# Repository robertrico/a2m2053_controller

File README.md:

# A2M2053 Controller

A replacement controller board for the Apple UniDisk 3.5 (A2M2053).

## Overview

The UniDisk 3.5 is Apple's 800K drive for the Apple II. When its controller
board (IF-83, service part 661-0307) dies, there's nothing to fix it with. The
board is built around a Sony CXD1013 gate array that has no public datasheet
and no replacement, and the only spare board on eBay has sat unsold at $150
for months.

This project replaces the whole board. A Raspberry Pi RP2350 speaks SmartPort
to the Apple IIe through the Liron card and drives the stock Sony 800K
mechanism directly through its 20-pin connector. The 65C02, ROM, RAM, IWM and
the CXD1013 are all gone. The mechanism, the case and the front panel stay.

It isn't a clone of the original. The firmware is new C on the Pico SDK. The
original drive ROM is used as a test oracle for SmartPort behavior, status
codes, errors and timing, never as a template.

## Features

- SmartPort device on the Liron card: STATUS, READBLOCK, WRITEBLOCK, FORMAT,
  CONTROL (eject), INIT
- Reads, writes and formats 800K double-sided ProDOS disks
- Daisy chain out the rear DB-19, in front of or behind another drive
- Front-panel eject button and in-use LED
- Runs from the Apple's own +5V and +12V rails through the host cable
- Whole-track read buffer on its own core; every write verified on the next
  revolution
- USB console for bring-up: mechanism status, raw flux capture, block reads,
  whole-disk scans, bus counters

## Scope

Apple IIe with 800K double-sided ProDOS disks. Macintosh disks (524-byte
blocks, Mac interleave) and 400K single-sided disks show up in Apple's docs
and the drive ROM but were never used on the IIe, so they're out of scope.

## Specifications

| Parameter | Value |
|---|---|
| MCU | RP2350A on a Raspberry Pi Pico 2 (prototype) |
| Level shifting | 5x SN74LVC8T245, 3.3V to 5V, one DIR and /OE per 8 channels |
| GPIO | 25 of 26 used |
| Host interface | SmartPort, Liron card DB-19 (CN102) |
| Mechanism interface | Sony 800K 20-pin (CN104, ERS 699-0321) |
| Mechanism | Stock Sony 800K double-sided, CX23077A logic + CX20185 read/write amp |
| Rear port | DB-19 daisy chain: PH3_OUT, ENBL_OUT, LASTONE/ |
| Power | +5V and +12V from the host connector; Pico VSYS from +5V through a diode |

## Architecture

```
 Apple IIe / Liron card                                  Sony 800K mechanism
         | DB-19                                                | 20-pin
   [level shifters]                                    [level shifters]
         |                                                      |
   PIO0: SmartPort FM rx/tx                     PIO1: flux capture / GCR write
   PIO2: rear-port pass-through                                 |
         |                                                      |
   CORE 0: SmartPort device  <---- block request queue ---->  CORE 1: mechanism
   - bus phases, packets                                      - status, seek, motor, eject
   - commands, DIB, status                                    - speed zones
   - daisy-chain ID, LASTONE/                                 - whole-track buffer
                                                              - GCR decode/encode
```

Each SmartPort read, write or format becomes a request to core 1. Core 0
holds ACK until the answer is back, and the Liron card waits.

## Project status

**Perfboard prototype: done** (October 2026). Milestones M0 to M9 passed on
the bench with a Pico 2, five 8T245 breakout boards and a mechanism from a
dead UniDisk.

| Milestone | What | Log |
|---|---|---|
| M0 | Bench rig, power, shifter boot safety | [m0](docs/build_log/m0.md) |
| M1 | Mechanism status reads | [m1](docs/build_log/m1.md) |
| M2 | Mechanism commands: motor, seek, eject | [m2](docs/build_log/m2.md) |
| M3 | Raw flux capture, decoded on the Mac | [m3](docs/build_log/m3.md) |
| M4 | Whole disk read on the board | [m4](docs/build_log/m4.md) |
| M5 | Write and format; the working UniDisk reads our disk | [m5](docs/build_log/m5.md) |
| M6 | SmartPort on the RP2350; ProDOS boots from a RAM disk | [m6](docs/build_log/m6.md) |
| M7 | ProDOS boots from a real floppy through the Liron card | [m7](docs/build_log/m7.md) |
| M7.5 | Bench supply retired; runs on the IIe rails | [m7_5](docs/build_log/m7_5.md) |
| M8 | Daisy chain with a working UniDisk, both orders | [m8](docs/build_log/m8.md) |
| M9 | Disk swaps, write-protect, ejects, resets, long runs | [m9](docs/build_log/m9.md) |

**Drop-in PCB: in design.** The outline matches the IF-83 and fits the
original mounting holes and case opening (checked with 3D prints). The board
must stay hand-solderable and well under the $150 the spare board couldn't
sell for. Requirements carried from the bench: [FABRICATION.md](FABRICATION.md).

Build notes and photos are also on
[bytehamr.com](https://bytehamr.com/projects/unidisk-controller/).

## Repository structure

```
a2m2053_controller/
├── firmware/            # RP2350 firmware (C, Pico SDK)
│   ├── src/             # SmartPort, mechanism server, PIO programs, console
│   └── test/            # Host-side unit tests (fake drive, simulated Liron card)
├── tools/
│   ├── a2m/             # Python: console client, flux decode, GCR, PIO model
│   ├── apple/           # Test disk builders and SPCOMPARE (Applesoft)
│   └── tests/           # pytest
├── hardware/kicad/      # KiCad schematic and PCB
├── docs/
│   ├── build_log/       # Per-milestone notes and measurements
│   ├── captures/        # Scope shots, Apple screens, console logs
│   ├── photos/          # Bench photos
│   ├── superpowers/specs/  # Design spec
│   ├── research_notes.md   # Facts with sources; start here
│   ├── level_shifting.md   # Signal directions and shifter grouping
│   └── pin_budget.md       # GPIO map
└── FABRICATION.md       # PCB requirements and part choices
```

## Getting started

### Prerequisites

- [Pico SDK](https://github.com/raspberrypi/pico-sdk) 2.2.0, CMake, Ninja,
  arm-none-eabi-gcc
- A Raspberry Pi Debug Probe (or picoprobe) and Raspberry Pi's OpenOCD build
  for SWD flashing
- Python 3 for the tools (`tools/requirements.txt`)
- [AppleCommander](https://applecommander.github.io/) and
  [ADTPro](https://adtpro.com/) for the test disks

### Building and flashing

```bash
cd firmware
make            # build
make test       # host-side unit tests
make flash      # program over SWD (OpenOCD)
make reset      # reset the target
```

Tool paths live in `.env.local` at the repo root, git-ignored. Copy
`.env.example`, fill in `PICO_SDK_PATH` and, if they are not on your PATH,
`OPENOCD` and `GDB`. Anything already in your environment or on the `make`
command line wins over the file. The test-disk scripts in `tools/apple/` read
`AC_JAR` and `PRODOS_SRC` from the same file.

### Console

The firmware exposes a USB CDC console. `help` lists the commands: mechanism
status and control, flux capture, block reads and writes, whole-disk scans,
format, and `sp` for the SmartPort bus state and counters. The Python tool
drives the console for the scripted jobs:

```bash
cd tools
python -m a2m.cli readdisk --port /dev/cu.usbmodemXXXX --out disk.po --compare ref.po
```

## Design references

This project builds on:

- [Byte Hamr](https://github.com/robertrico/project_byte_hamr): the PicoPort
  SmartPort device for the RP2040 (the FM receive/transmit PIO programs and
  packet layout started there), its IWM work, and the annotated drive ROM
  disassembly by Eric Smith used as the oracle.
- [bitsavers](http://www.bitsavers.org/pdf/apple/disk/sony/): Sony 800K
  drive ERS (699-0321), mechanism schematics, Apple drive command and status
  codes.
- [tashnotes](https://github.com/lampmerchant/tashnotes): GCR checksum and
  drive command tables.
- Apple II Technical Notes (UniDisk 3.5 #1-#5, Misc #6) and the IWM
  specifications, via the [Asimov archive](https://www.apple.asimov.net/).

Datasheets, Apple and Sony documents, and photos of other people's boards
were used during the work but aren't ours to host, so they're not in this
repo. [docs/SOURCES.md](docs/SOURCES.md) says where each one came from.

## License

This project is released under the [MIT License](LICENSE.md).

## Author

Robert Rico

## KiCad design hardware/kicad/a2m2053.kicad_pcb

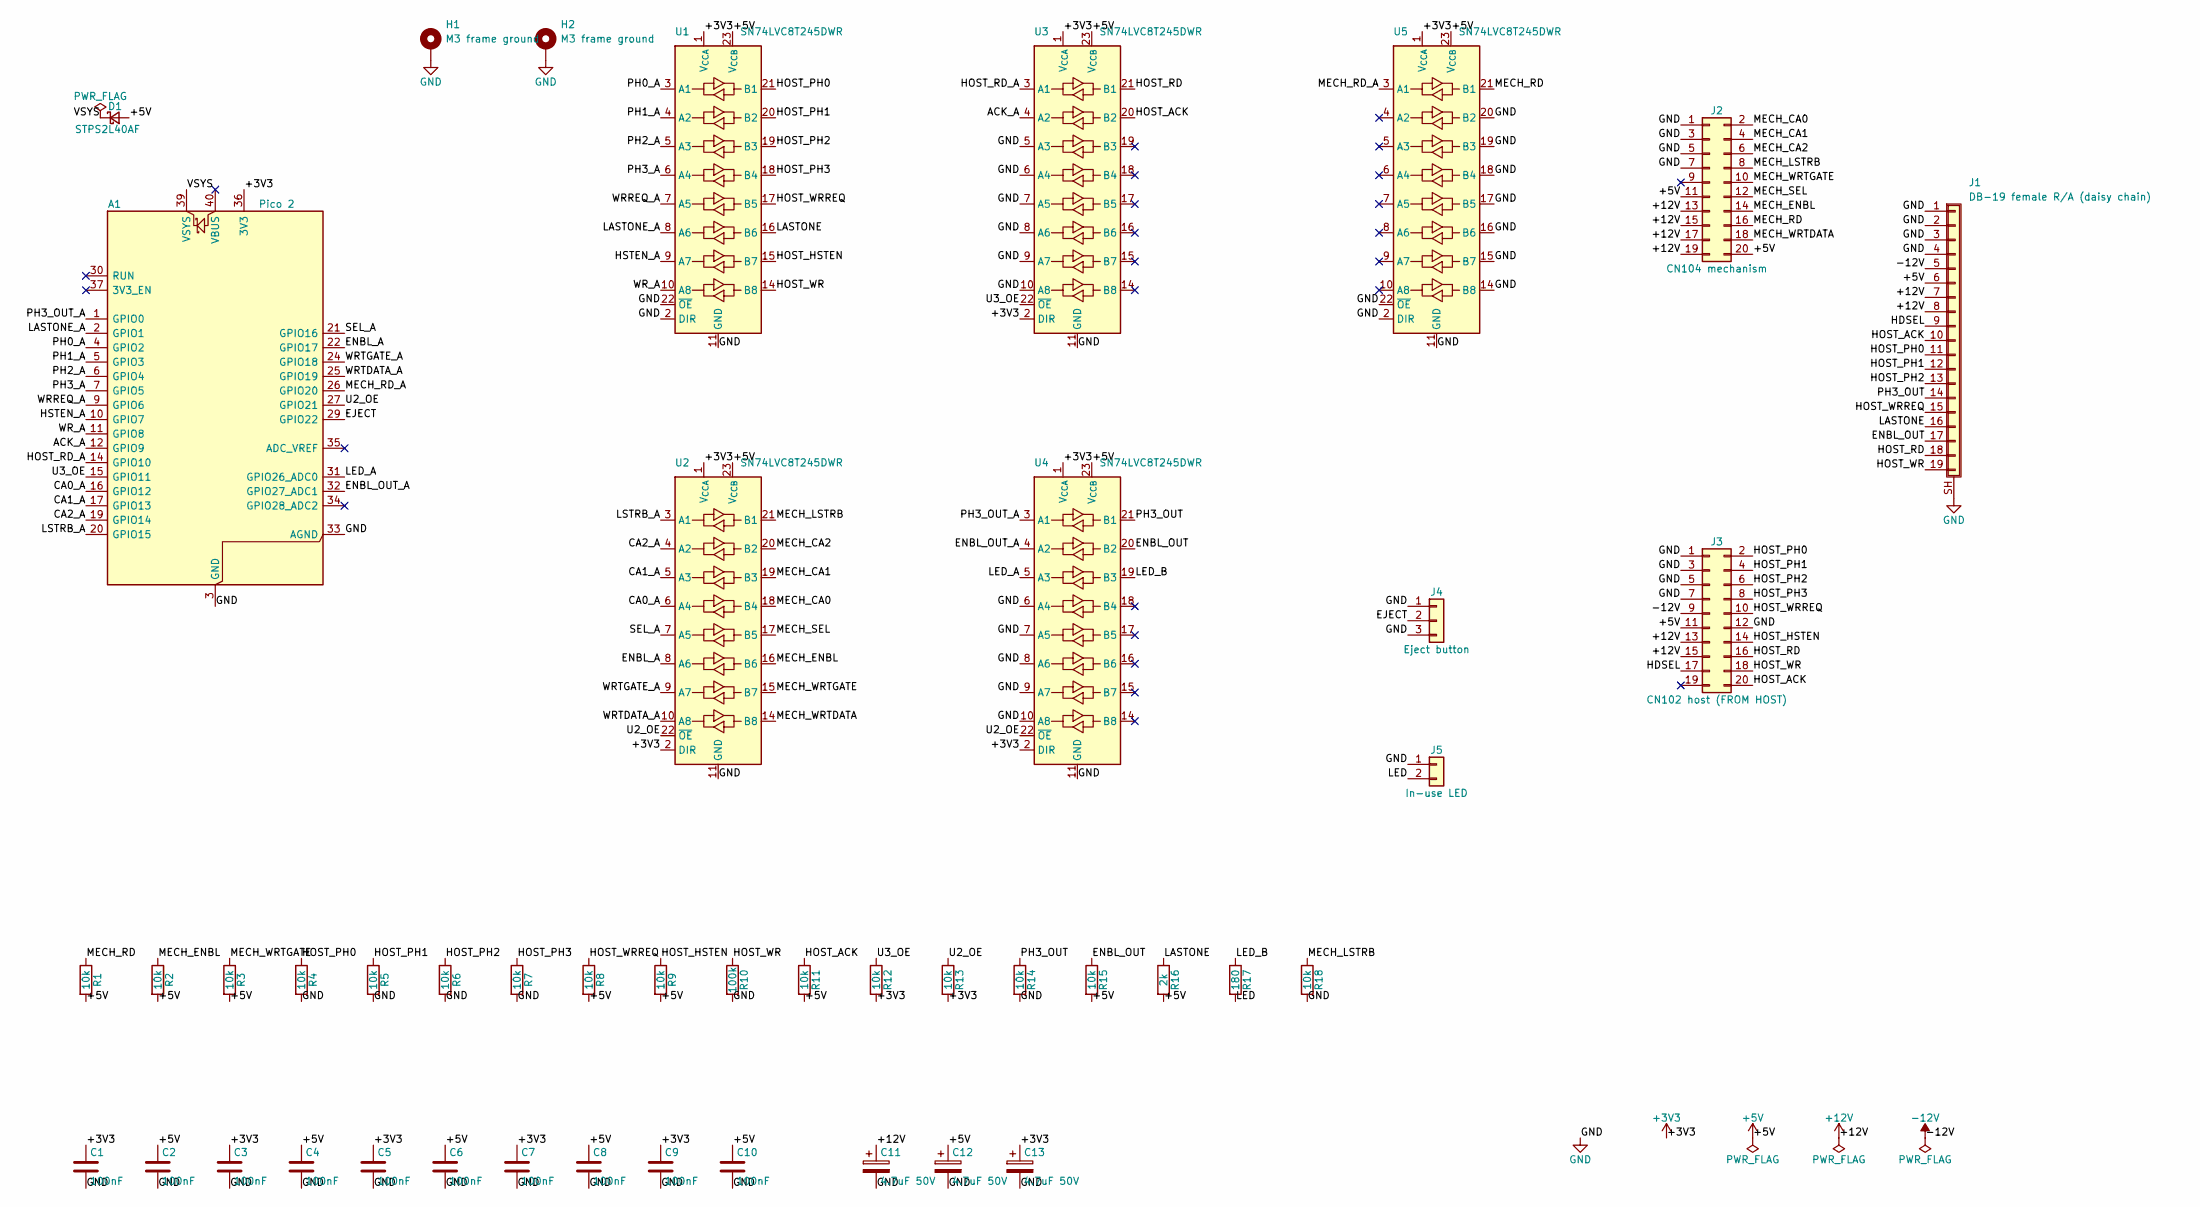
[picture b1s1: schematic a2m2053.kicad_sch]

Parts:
A1: Pico 2; RaspberryPi_Pico_SMD_HandSolder
C1, C2, C3, C4, C5, C6, C7, C8, C9, C10: 100nF; C_0805_2012Metric
C11, C12, C13: 4.7uF 50V; CP_Radial_D5.0mm_P2.00mm
D1: STPS2L40AF; D_SMA
H1: M3 frame ground; MountingHole_3.2mm_M3_Pad_5.2mm
H2: M3 frame ground; MountingHole_3.2mm_M3_Pad_Via
J1: DB-19 female R/A (daisy chain); DSUB-19_Female_Horizontal_P2.77x2.84mm_MountingHoles38.8mm
J2: CN104 mechanism; IDC-Header_2x10_P2.54mm_Vertical
J3: CN102 host (FROM HOST); IDC-Header_2x10_P2.54mm_Vertical
J4: Eject button; TE_AMP_CT_1x03_P2.00mm_Vertical; MPN 292161-3
J5: In-use LED; TE_AMP_CT_1x02_P2.00mm_Vertical; MPN 292161-2
R1, R2, R3, R4, R5, R6, R7, R8, R9, R11, R12, R13, R14, R15, R18: 10k; R_1206_3216Metric
R10: 100k; R_1206_3216Metric
R16: 2k; R_1206_3216Metric
R17: 180; R_1206_3216Metric
U1, U2, U3, U4, U5: SN74LVC8T245DWR; SOIC-24W_7.5x15.4mm_P1.27mm

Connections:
+3V3: A1.36 (3V3), C1.1, C3.1, C5.1, C7.1, C9.1, C13.1, R12.2, R13.2, U1.1 (V_{CCA}), U2.1 (V_{CCA}), U2.2 (DIR), U3.1 (V_{CCA}), U3.2 (DIR), U4.1 (V_{CCA}), U4.2 (DIR), U5.1 (V_{CCA})
/ACK_A: A1.12 (GPIO9), U3.4 (A2)
/CA0_A: A1.16 (GPIO12), U2.6 (A4)
/CA1_A: A1.17 (GPIO13), U2.5 (A3)
/CA2_A: A1.19 (GPIO14), U2.4 (A2)
/EJECT: A1.29 (GPIO22), J4.2
/ENBL_A: A1.22 (GPIO17), U2.8 (A6)
/ENBL_OUT: J1.17, R15.1, U4.20 (B2)
/ENBL_OUT_A: A1.32 (GPIO27_ADC1), U4.4 (A2)
/HDSEL: J1.9, J3.17
/HOST_ACK: J1.10, J3.20, R11.1, U3.20 (B2)
/HOST_HSTEN: J3.14, R9.1, U1.15 (B7)
/HOST_PH0: J1.11, J3.2, R4.1, U1.21 (B1)
/HOST_PH1: J1.12, J3.4, R5.1, U1.20 (B2)
/HOST_PH2: J1.13, J3.6, R6.1, U1.19 (B3)
/HOST_PH3: J3.8, R7.1, U1.18 (B4)
/HOST_RD: J1.18, J3.16, U3.21 (B1)
/HOST_RD_A: A1.14 (GPIO10), U3.3 (A1)
/HOST_WR: J1.19, J3.18, R10.1, U1.14 (B8)
/HOST_WRREQ: J1.15, J3.10, R8.1, U1.17 (B5)
/HSTEN_A: A1.10 (GPIO7), U1.9 (A7)
/LASTONE: J1.16, R16.1, U1.16 (B6)
/LASTONE_A: A1.2 (GPIO1), U1.8 (A6)
/LED: J5.2, R17.2
/LED_A: A1.31 (GPIO26_ADC0), U4.5 (A3)
/LED_B: R17.1, U4.19 (B3)
/LSTRB_A: A1.20 (GPIO15), U2.3 (A1)
/MECH_CA0: J2.2, U2.18 (B4)
/MECH_CA1: J2.4, U2.19 (B3)
/MECH_CA2: J2.6, U2.20 (B2)
/MECH_ENBL: J2.14, R2.1, U2.16 (B6)
/MECH_LSTRB: J2.8, R18.1, U2.21 (B1)
/MECH_RD: J2.16, R1.1, U5.21 (B1)
/MECH_RD_A: A1.26 (GPIO20), U5.3 (A1)
/MECH_SEL: J2.12, U2.17 (B5)
/MECH_WRTDATA: J2.18, U2.14 (B8)
/MECH_WRTGATE: J2.10, R3.1, U2.15 (B7)
/PH0_A: A1.4 (GPIO2), U1.3 (A1)
/PH1_A: A1.5 (GPIO3), U1.4 (A2)
/PH2_A: A1.6 (GPIO4), U1.5 (A3)
/PH3_A: A1.7 (GPIO5), U1.6 (A4)
/PH3_OUT: J1.14, R14.1, U4.21 (B1)
/PH3_OUT_A: A1.1 (GPIO0), U4.3 (A1)
/SEL_A: A1.21 (GPIO16), U2.7 (A5)
/U2_OE: A1.27 (GPIO21), R13.1, U2.22 (~OE), U4.22 (~OE)
/U3_OE: A1.15 (GPIO11), R12.1, U3.22 (~OE)
/WRREQ_A: A1.9 (GPIO6), U1.7 (A5)
/WRTDATA_A: A1.25 (GPIO19), U2.10 (A8)
/WRTGATE_A: A1.24 (GPIO18), U2.9 (A7)
/WR_A: A1.11 (GPIO8), U1.10 (A8)
GND: A1.3 (GND), A1.8 (GND), A1.13 (GND), A1.18 (GND), A1.23 (GND), A1.28 (GND), A1.33 (AGND), A1.38 (GND), C1.2, C2.2, C3.2, C4.2, C5.2, C6.2, C7.2, C8.2, C9.2, C10.2, C11.2, C12.2, C13.2, H1.1 (1_1), H2.1 (1_1), J1.1, J1.2, J1.3, J1.4, J1.SH (Shield), J2.1, J2.3, J2.5, J2.7, J3.1, J3.3, J3.5, J3.7, J3.12, J4.1, J4.3, J5.1, R4.2, R5.2, R6.2, R7.2, R10.2, R14.2, R18.2, U1.2 (DIR), U1.11 (GND), U1.12 (GND), U1.13 (GND), U1.22 (~OE), U2.11 (GND), U2.12 (GND), U2.13 (GND), U3.5 (A3), U3.6 (A4), U3.7 (A5), U3.8 (A6), U3.9 (A7), U3.10 (A8), U3.11 (GND), U3.12 (GND), U3.13 (GND), U4.6 (A4), U4.7 (A5), U4.8 (A6), U4.9 (A7), U4.10 (A8), U4.11 (GND), U4.12 (GND), U4.13 (GND), U5.2 (DIR), U5.11 (GND), U5.12 (GND), U5.13 (GND), U5.14 (B8), U5.15 (B7), U5.16 (B6), U5.17 (B5), U5.18 (B4), U5.19 (B3), U5.20 (B2), U5.22 (~OE)

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
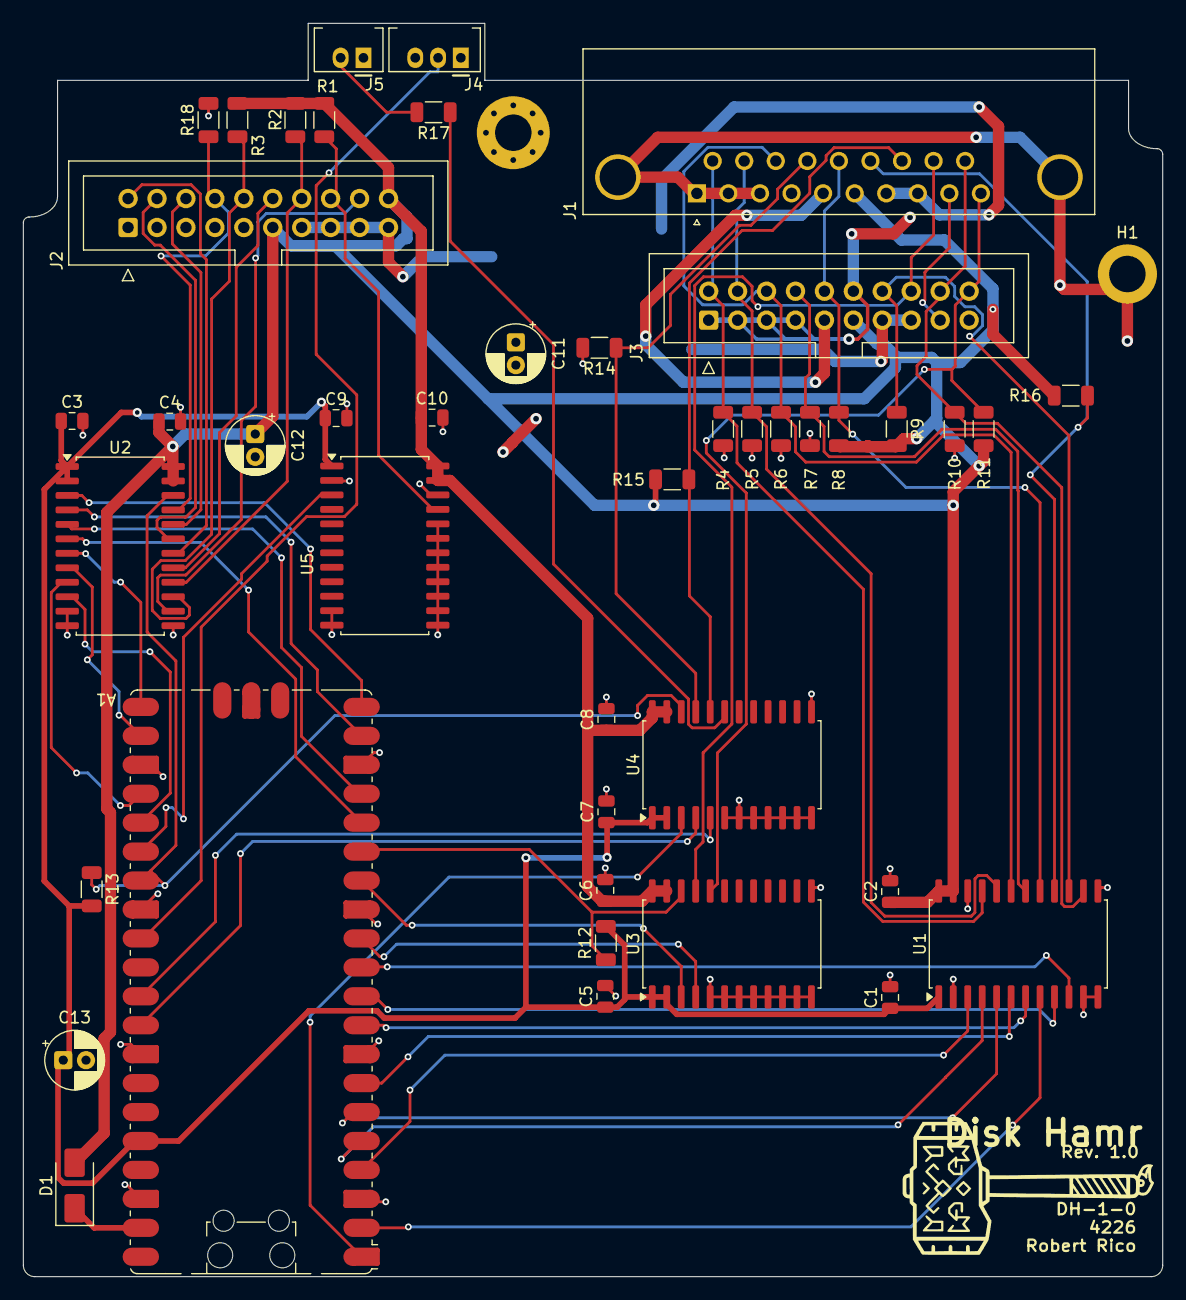
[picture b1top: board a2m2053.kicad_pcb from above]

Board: 2 copper layers, 100.0 x 110.0 mm, 45 parts (0 on the bottom side), 55 nets.

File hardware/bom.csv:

Item,Qty,References,Value,Package / footprint,Manufacturer,MPN,Vendor,Vendor part,Est. unit USD (unverified; see bom.md),Notes
1,1,A1,Pico 2,Castellated module (RaspberryPi_Pico_SMD_HandSolder),Raspberry Pi,SC1631,Digikey,2648-SC1631CT-ND,6.12,"Plain Pico 2, no headers, not W. Soldered flat by castellations. $12 min per unit (Rico 2026-10-18)."
2,5,"U1,U2,U3,U4,U5",SN74LVC8T245DWR,SOIC-24W 7.5 mm 1.27 mm,Texas Instruments,SN74LVC8T245DWR,Digikey,296-23280-1-ND,1.10,"Level shifters. Alternates (TSSOP, respin): 74LVC8T245PW, SN74LXC8T245PWR."
3,1,D1,STPS2L40AF,SMA,STMicroelectronics,STPS2L40AF,Digikey,497-18870-1-ND,0.63,"Pico VSYS feed from IIe +5V, blocks USB back-feed. Any 2 A low-Vf SMA Schottky."
4,10,"C1,C2,C3,C4,C5,C6,C7,C8,C9,C10",100nF 50V X7R,0805,Samsung,CL21B104KBCNNNC,Digikey,1276-1003-1-ND,0.03,"Decoupling, one VCCA and one VCCB per shifter. Order 15."
5,3,"C11,C12,C13",4.7uF 50V electrolytic,Radial D5 mm P2.0 mm,Panasonic,ECA-1HM4R7,Digikey,P5177-ND,0.145,"Bulk at CN104 (+12V, +5V) as on the IF-83, and 3V3 bulk. Polarized."
6,15,"R1,R2,R3,R4,R5,R6,R7,R8,R9,R11,R12,R13,R14,R15,R18",10k,1206,Yageo,RC1206FR-0710KL,Digikey,311-10.0KFRCT-ND,0.02,"Pull-ups and pull-downs, see bom.md for each net. Order 20."
7,1,R10,100k,1206,Yageo,RC1206FR-07100KL,Digikey,311-100KFRCT-ND,0.02,"Host WR pull-down. 100k not 10k (measured, m6)."
8,1,R16,2k,1206,Yageo,RC1206FR-072KL,Digikey,311-2.00KFRCT-ND,0.02,"LASTONE/ pull-up on the rear port, pin 16."
9,1,R17,180,1206,Yageo,RC1206FR-07180RL,Digikey,311-180FRCT-ND,0.02,"In-use LED series resistor. Same value as the IF-83 LED anode pull-up (180 ohm, measured 2026-10-25). About 17 mA from 5 V, inside the 8T245 32 mA rating."
10,1,J1,DB-19 female right angle PCB mount,D-sub 19 with board locks 38.8 mm apart,-,-,eBay / AliExpress,"""DB19 female right angle""",15.00,"Rear daisy-chain port. Rarest and most expensive part on the board, $15 each on eBay. Purchased; fit-tested in the printed outline and the case opening, M7.2 2026-10-14."
11,2,"J2,J3",2x10 shrouded box header 2.54 mm vertical,IDC-Header_2x10_P2.54mm_Vertical,Wurth,61202021621,Digikey,732-2096-ND,0.885,"J2 = CN104 mechanism ribbon, J3 = CN102 host ribbon."
12,1,J4,AMP CT header 1x3 2.0 mm vertical,TE_AMP_CT_1x03_P2.00mm_Vertical (custom),TE Connectivity,292161-3,Digikey,A98589-ND,0.72,"Eject button (CN108). Black alternate 6-292161-3. Mates the drive's own lead (TE 173977 receptacle)."
13,1,J5,AMP CT header 1x2 2.0 mm vertical,TE_AMP_CT_1x02_P2.00mm_Vertical (custom),TE Connectivity,292161-2,Digikey,A98588-ND,0.38,"In-use LED (CN107). Black alternate 6-292161-2. Mates the drive's own lead."
14,2,"H1,H2",M3 mounting hole,3.2 mm plated on GND,-,-,-,-,0.00,"Drive's own M3 screws and standoffs. Not a purchased part."
15,1,PCB,Disk Hamr rev 1.0,2 layer 100 x 110 mm 1.6 mm FR-4,-,-,JLCPCB / PCBWay / OSH Park,-,6.00,"Min track 0.25, clearance 0.2, drill 0.3. ENIG preferred. Qty 5 pricing."

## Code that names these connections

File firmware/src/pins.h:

#pragma once
// GPIO map: docs/pin_budget.md. Shifters: U1 (B->A, always on),
// U2 + U4 (A->B, /OE = PIN_MECH_OE), U3 (A->B, /OE = PIN_HOST_RD_OE), U5 (B->A).
#define PIN_PH3_OUT       0
#define PIN_LASTONE       1
#define PIN_PH0           2
#define PIN_PH1           3
#define PIN_PH2           4
#define PIN_PH3           5
#define PIN_HOST_WRREQ    6
#define PIN_HOST_HSTEN    7
#define PIN_HOST_WR       8
#define PIN_ACK           9   // via U3 with host RD; valid only while PIN_HOST_RD_OE is low
#define PIN_HOST_RD      10
#define PIN_HOST_RD_OE   11   // U3 /OE, active low
#define PIN_CA0          12
#define PIN_CA1          13
#define PIN_CA2          14
#define PIN_LSTRB        15
#define PIN_SEL          16
#define PIN_MECH_ENBL    17   // /ENBL, active low
#define PIN_MECH_WRTGATE 18   // /WRTGATE, active low. Driven only by flux_tx.c (M5).
#define PIN_MECH_WRTDATA 19
#define PIN_MECH_RD      20   // read data + status (CA0-2/SEL select)
#define PIN_MECH_OE      21   // U2 + U4 /OE, active low, 10k pull-up to 3V3
#define PIN_EJECT_BTN    22
#define PIN_LED          26
#define PIN_ENBL_OUT     27
